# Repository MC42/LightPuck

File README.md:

# LightPuck
WS2812B carrier board to use with the new WPILib DIO-based driver software.

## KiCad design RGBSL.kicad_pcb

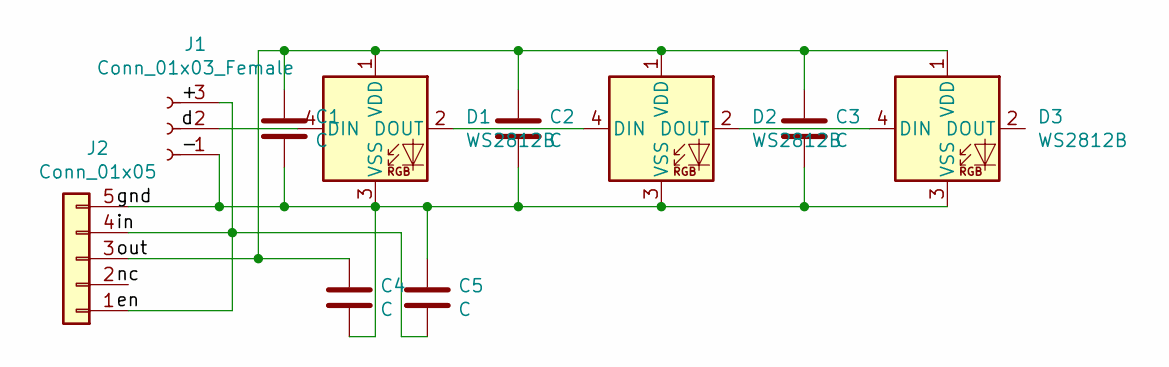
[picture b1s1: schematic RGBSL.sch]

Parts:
C1, C2, C3, C4, C5: C; C_0805_2012Metric_Pad1.15x1.40mm_HandSolder
D1, D2, D3: WS2812B; LED_WS2812B_PLCC4_5.0x5.0mm_P3.2mm
J1: Conn_01x03_Female; PinSocket_1x03_P2.54mm_Vertical
J2: Conn_01x05; SOT-223-5

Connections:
unnamed: C1.1, C2.1, C3.1, C4.1, D1.1 (VDD), D2.1 (VDD), D3.1 (VDD), J2.3
unnamed: C1.2, C2.2, C3.2, C4.2, C5.1, D1.3 (VSS), D2.3 (VSS), D3.3 (VSS), J1.1, J2.5
unnamed: C5.2, J1.3, J2.1, J2.4
unnamed: D1.2 (DOUT), D2.4 (DIN)
unnamed: D1.4 (DIN), J1.2
unnamed: D2.2 (DOUT), D3.4 (DIN)

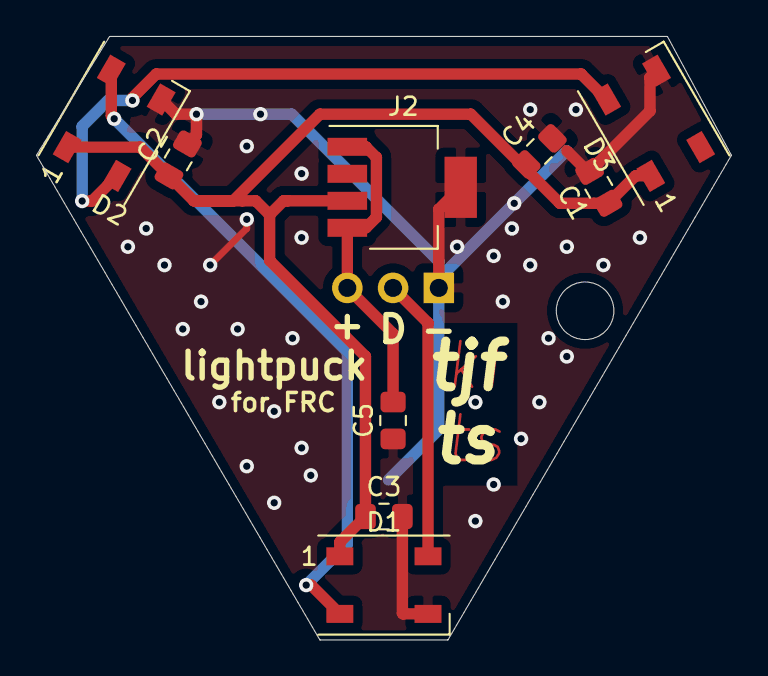
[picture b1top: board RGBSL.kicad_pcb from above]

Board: 2 copper layers, 38.6 x 33.5 mm, 10 parts (1 on the bottom side), 6 nets.

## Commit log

2019-12-07 I got bored
2019-12-07 Adding gerbers
2019-12-07 Updated new version, larger and better than ever.
2019-12-08 Added latest version withs lightly optimized traces.
